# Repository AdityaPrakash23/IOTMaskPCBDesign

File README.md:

# IOTMaskPCBDesign
KiCAD design files for IoT Mask Project

This is a compact (disk of 30cm) design using ESP32 Pico D4 microcontroller.

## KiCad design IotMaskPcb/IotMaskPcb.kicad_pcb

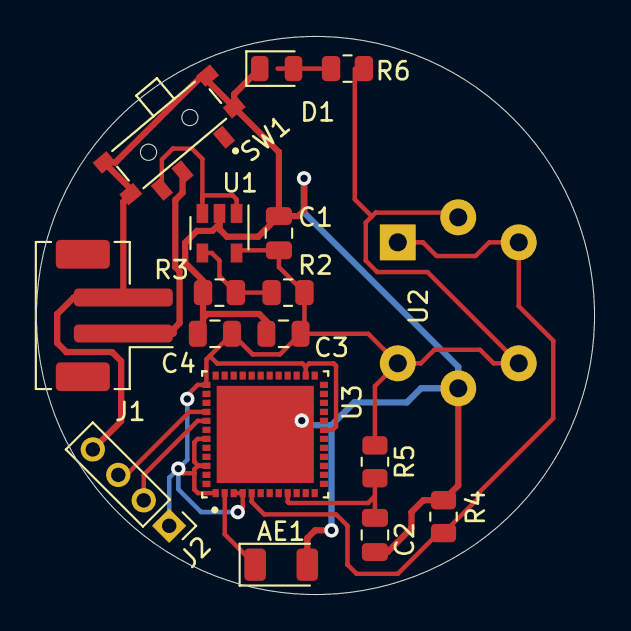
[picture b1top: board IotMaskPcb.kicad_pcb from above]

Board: 2 copper layers, 31.0 x 31.0 mm, 17 parts (1 on the bottom side), 11 nets.

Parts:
AE1: 2.4GHz; Johanson_2450AT18x100
C1: 10nF; C_0805_2012Metric
C2: 1uF; C_0805_2012Metric
C3: 10uF; C_0805_2012Metric
C4: 0.1uF; C_0805_2012Metric
D1: 7012x1; LED_0805_2012Metric
J1: Lipo; JST_PH_B2B-PH-SM4-TB_1x02-1MP_P2.00mm_Vertical
J2: UART; PinHeader_1x04_P2.00mm_Vertical
R2: 22k; R_0805_2012Metric
R3, R4, R5: 10k; R_0805_2012Metric
R6: 1k; R_0805_2012Metric
SW1: MLL1200S; SW_MLL1200S
U1: SPX; SOT-23-5
U2: MQ-135; MQ-6
U3: ESP; PQFN50P700X700X104-49N

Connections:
/3.3V: C1.1, C3.2, C4.2, J2.1, R2.1, R5.1, R6.1, U1.5, U2.2, U2.4, U2.6, U3.1, U3.3, U3.4, U3.19, U3.26, U3.37, U3.43, U3.46
/5V: J1.1, SW1.2
/Rx: J2.3, U3.40
/Tx: J2.2, U3.41
ADC: R4.1, U2.1, U2.3, U3.5
GND: AE1.2, C1.2, C2.2, C3.1, C4.1, D1.1, J1.2, J2.4, R3.2, R4.2, SW1.G1, SW1.G2, SW1.G3, SW1.G4, U1.2, U2.5, U3.49
unnamed: AE1.1, U3.2
unnamed: C2.1, R5.2, U3.9
unnamed: D1.2, R6.2
unnamed: R2.2, R3.1, U1.4
unnamed: SW1.3, U1.1, U1.3

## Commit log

2021-05-23 Project files for IOT Mask project
    This contains completed KiCAD Design files, datasheets and external KiCAD packages for specific components.
